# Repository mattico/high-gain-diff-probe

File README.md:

# High Gain Differential Probe

This was my attempt at a high gain (2000X) low-noise differential probe, for use in electronics testing.

Be warned that I haven't gotten this working. IIRC the issue was that it would oscillate or saturate. I didn't look into it too thoroughly, it's possible that there is an easy fix.

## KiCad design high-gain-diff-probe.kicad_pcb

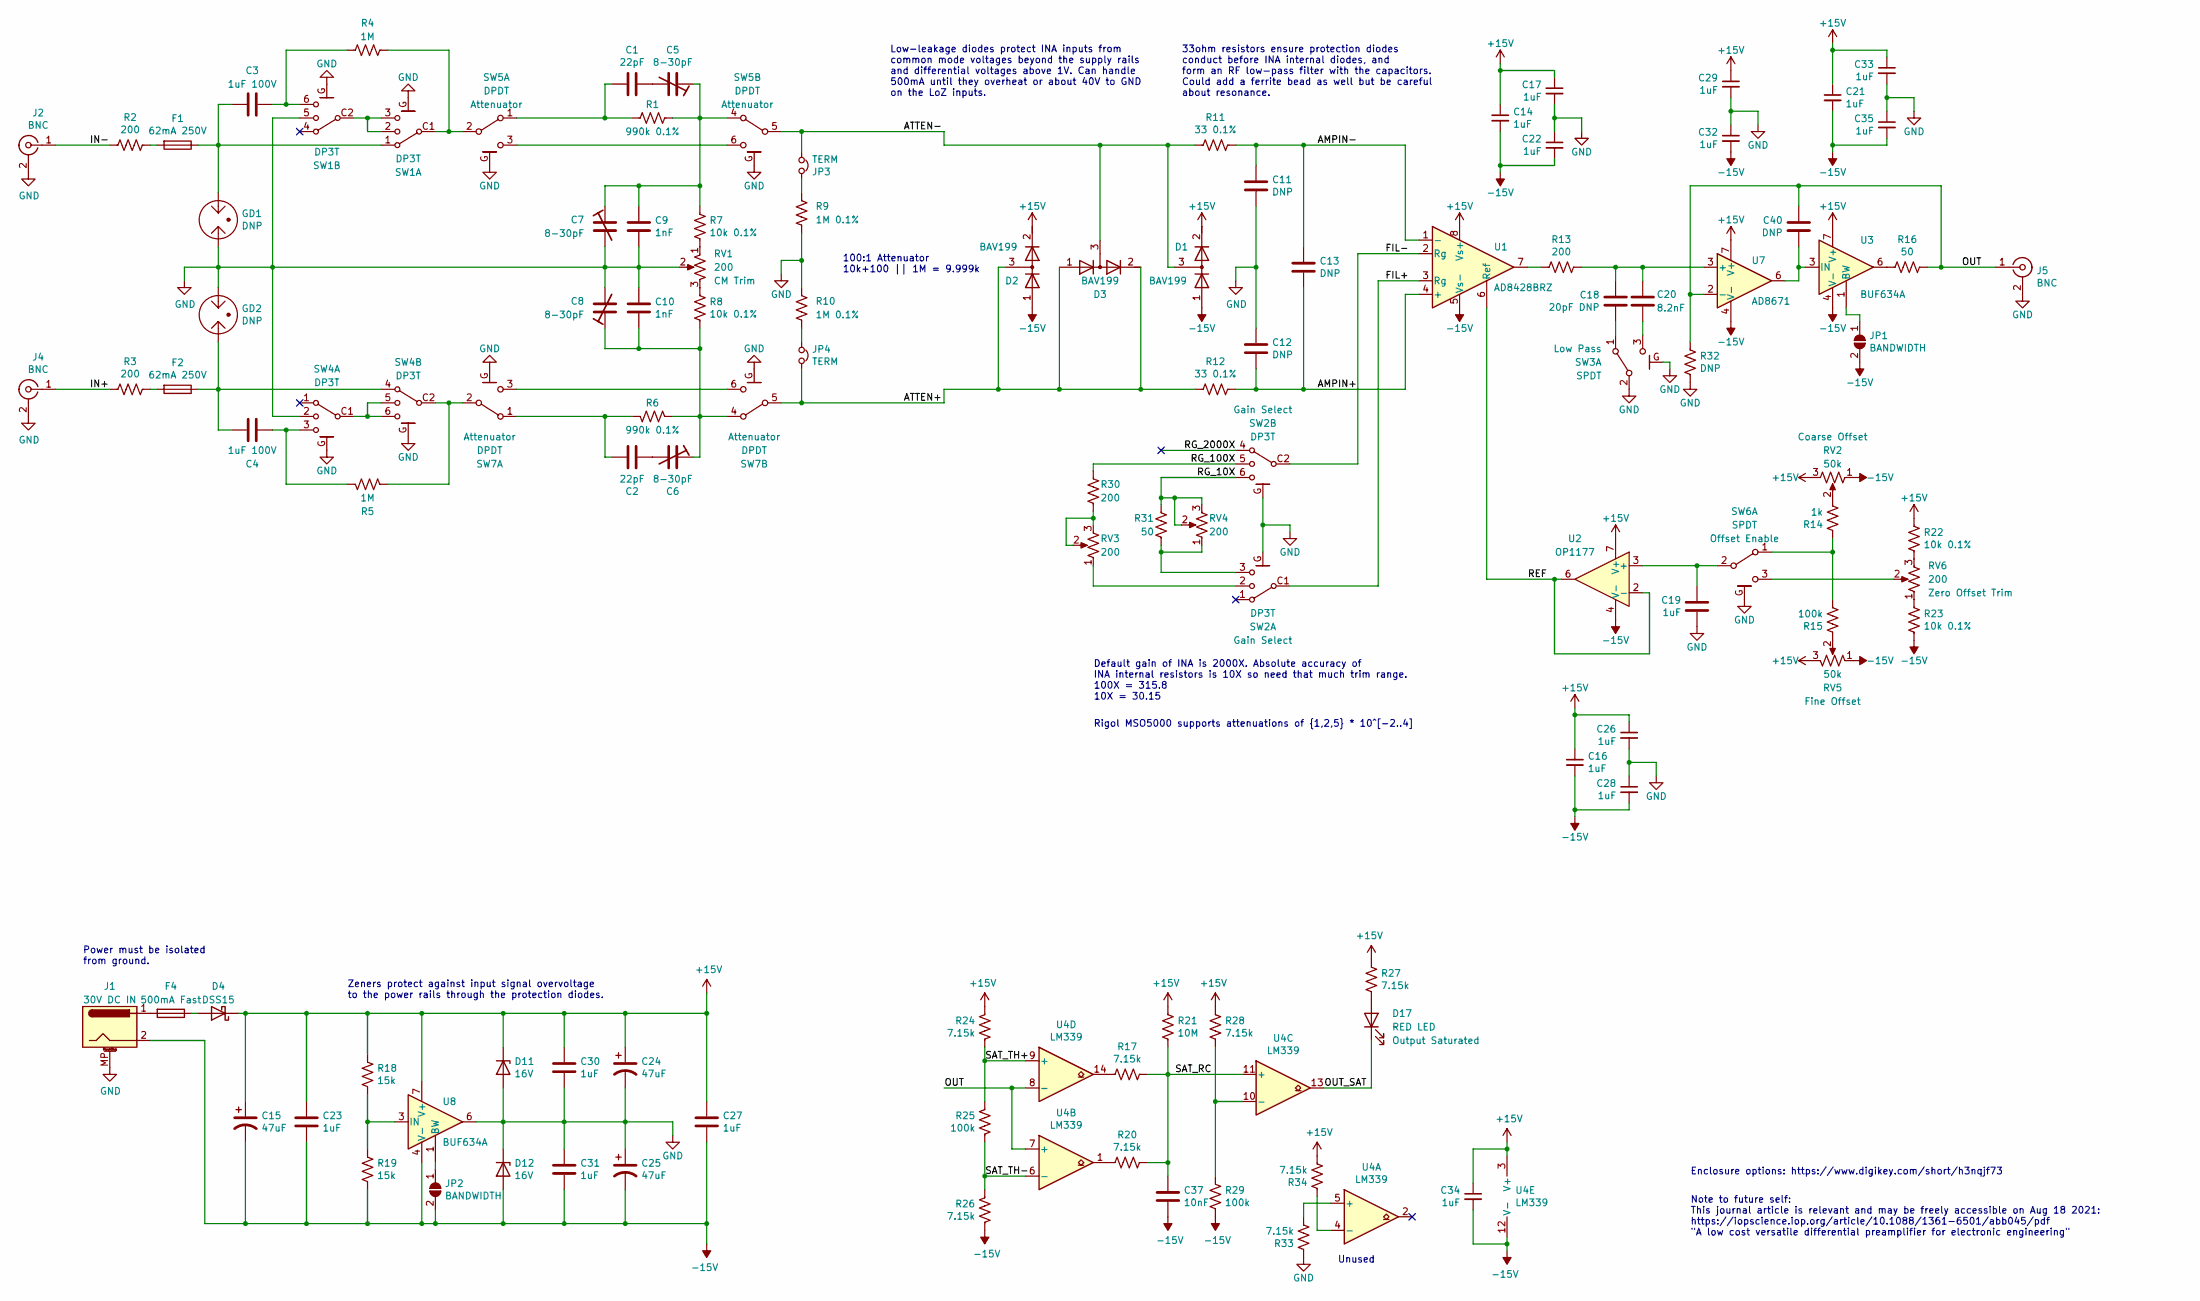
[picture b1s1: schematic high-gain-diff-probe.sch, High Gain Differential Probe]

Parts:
C1, C2: 22pF; C_0805_2012Metric_Pad1.15x1.40mm_HandSolder; MPN C0805C220J1GACTU
C3, C4: 1uF 100V; C_Rect_L7.2mm_W7.2mm_P5.00mm_FKS2_FKP2_MKS2_MKP2; MPN R82EC4100SH70J
C5, C6, C7, C8: 8-30pF; C_Trimmer_Voltronics_JZ; MPN SGC3S300
C9, C10: 1nF; C_0603_1608Metric_Pad1.05x0.95mm_HandSolder; MPN 0603N102F500CT
C11, C12, C13, C40: DNP; C_0603_1608Metric_Pad1.05x0.95mm_HandSolder
C14, C16, C17, C19, C21, C22, C23, C26, C27, C28, C29, C30, C31, C32, C33, C34, C35: 1uF; C_0603_1608Metric_Pad1.05x0.95mm_HandSolder; MPN CL10A105KL8NNNC
C15, C24, C25: 47uF; CP_Elec_6.3x7.7; MPN A768EB476M1VLAE042
C18: 20pF DNP; C_0603_1608Metric_Pad1.05x0.95mm_HandSolder
C20: 8.2nF; C_0603_1608Metric_Pad1.05x0.95mm_HandSolder; MPN GRM1885C1H822JA01D
C37: 10nF; C_0603_1608Metric_Pad1.05x0.95mm_HandSolder; MPN GRM188R72A103KA01J
D1, D2, D3: BAV199; SOT-23; MPN BAV199,215
D4: DSS15; D_SOD-123; MPN DSS15UTR
D11, D12: 16V; D_SMF; MPN BZD27C16
D17: RED LED; LED_D5.0mm; MPN 151051RS11000
F1, F2: 62mA 250V; Fuseholder_Cylinder-5x20mm_Schurter_FAB_0031-355x_Horizonta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; MPN 0031.3577
F4: 500mA Fast; Fuse_0805_2012Metric_Pad1.15x1.40mm_HandSolder; MPN F0805B0R50FWTR
GD1, GD2: DNP; GDT_Bourns_2031; MPN 2031-15T
J1: 30V DC IN; BarrelJack_CUI_PJ-063AH_Horizontal; MPN PJ-063AH
J2, J4, J5: BNC; BNC_Amphenol_B6252HB-NPP3G-50_Horizontal; MPN 0731385033
JP1, JP2: BANDWIDTH; SolderJumper-2_P1.3mm_Open_TrianglePad1.0x1.5mm
JP3, JP4: TERM; PinHeader_1x03_P2.54mm_Vertical; MPN PR20203VBNN
R1, R6: 990k 0.1%; R_1206_3216Metric_Pad1.30x1.75mm_HandSolder; MPN PTN1206E9903BST1
R2, R3: 200; R_MiniMELF_MMA-0204; MPN SMA-A0204BTNX180R
R4, R5: 1M; R_0603_1608Metric_Pad0.98x0.95mm_HandSolder; MPN RT0603BRD071ML
R7, R8, R22, R23: 10k 0.1%; R_0603_1608Metric_Pad0.98x0.95mm_HandSolder; MPN RT0603BRD1010KL
R9, R10: 1M 0.1%; R_0603_1608Metric_Pad0.98x0.95mm_HandSolder; MPN RT0603BRD071ML
R11, R12: 33 0.1%; R_0603_1608Metric_Pad0.98x0.95mm_HandSolder; MPN RT0603BRD0733RL
R13, R30: 200; R_0603_1608Metric_Pad0.98x0.95mm_HandSolder; MPN RMCF0603FT200R
R14: 1k; R_0603_1608Metric_Pad0.98x0.95mm_HandSolder; MPN CR0603-FX-1001ELF
R15, R25, R29: 100k; R_0603_1608Metric_Pad0.98x0.95mm_HandSolder; MPN RT0603FRE07100KL
R16: 50; R_1210_3225Metric_Pad1.30x2.65mm_HandSolder; MPN RMCF1210FT49R9
R17, R20, R24, R26, R27, R28, R33, R34: 7.15k; R_0603_1608Metric_Pad0.98x0.95mm_HandSolder; MPN RMCF0603FT7K15
R18, R19: 15k; R_0603_1608Metric_Pad0.98x0.95mm_HandSolder; MPN WR06X1502FTL
R21: 10M; R_0603_1608Metric_Pad0.98x0.95mm_HandSolder; MPN RMCF0603JT10M0
R31: 50; R_0603_1608Metric_Pad0.98x0.95mm_HandSolder; MPN RMCF0603FT49R9
R32: DNP; R_0603_1608Metric_Pad0.98x0.95mm_HandSolder
RV1, RV3, RV4, RV6: 200; Potentiometer_Bourns_3296Y_Vertical; MPN 67YR200LF
RV2, RV5: 50k; Potentiometer_Bourns_PTV09A-1_Single_Vertical; MPN PTV09A-4025F-B503
SW1, SW2, SW4: DP3T; SW_NKK_MRB24B; MPN MRB24B
SW3, SW6: SPDT; SW_TE_1825263-2_DPDT; MPN 1825263-2
SW5, SW7: DPDT; SW_TE_1825263-2_DPDT; MPN 1825263-2
U1: AD8428BRZ; SOIC-8_3.9x4.9mm_P1.27mm; MPN AD8428BRZ
U2: OP1177; SOIC-8_3.9x4.9mm_P1.27mm; MPN OP1177ARZ-REEL7
U3, U8: BUF634A; SOIC-8-1EP_3.9x4.9mm_P1.27mm_EP2.41x3.81mm_LargeThermalVias; MPN BUF634AIDDAR
U4: LM339; SOIC-14_3.9x8.7mm_P1.27mm; MPN NJM339CG-TE2
U7: AD8671; SOIC-8_3.9x4.9mm_P1.27mm; MPN AD8671ARZ-REEL7

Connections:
+15V: C14.1, C15.1, C16.1, C17.1, C21.1, C23.1, C24.1, C26.1, C27.1, C29.1, C30.1, C33.1, C34.1, D1.2 (K), D2.2 (K), D4.1 (K), D11.1 (K), R18.1, R21.2, R22.1, R24.2, R27.2, R28.2, R34.1, RV2.3, RV5.3, U1.8 (Vs+), U2.7 (V+), U3.7 (V+), U4.3 (V+), U7.7 (V+), U8.7 (V+)
-15V: C14.2, C15.2, C16.2, C21.2, C22.2, C23.2, C25.2, C27.2, C28.2, C31.2, C32.2, C34.2, C35.2, C37.1, D1.1 (A), D2.1 (A), D12.2 (A), J1.2, JP1.2 (B), JP2.2 (B), R19.2, R23.2, R26.1, R29.1, RV2.1, RV5.1, U1.5 (Vs-), U2.4 (V-), U3.4 (V-), U3.9 (PAD), U4.12 (V-), U7.4 (V-), U8.4 (V-), U8.9 (PAD)
/AMPIN+: C12.2, C13.2, R12.1, U1.4 (+)
/AMPIN-: C11.1, C13.1, R11.1, U1.1 (-)
/ATTEN+: D2.3 (common), D3.1 (A), D3.2 (K), JP4.2, R12.2, SW7.5 (B)
/ATTEN-: D1.3 (common), D3.3 (common), JP3.2, R11.2, SW5.5 (B)
/FIL+: SW2.C1 (C2), U1.3 (Rg)
/FIL-: SW2.C2, U1.2 (Rg)
/IN+: J4.1 (In), R3.2
/IN-: J2.1 (In), R2.2
/OUT: C40.1, J5.1 (In), R16.1, R32.1, U4.7 (+), U4.8 (-), U7.2 (-)
/OUT_SAT: D17.1 (K), U4.13
/REF: U1.6 (Ref), U2.2 (-), U2.6
/RG_10X: R31.2, RV4.2, RV4.3, SW2.6
/RG_100X: R30.1, SW2.5
/SAT_RC: C37.2, R17.1, R20.1, R21.1, U4.11 (+)
/SAT_TH+: R24.1, R25.2, U4.9 (+)
/SAT_TH-: R25.1, R26.2, U4.6 (-)
GND: C7.2, C8.2, C9.2, C10.1, C11.2, C12.1, C17.2, C19.1, C22.1, C24.2, C25.1, C26.2, C28.1, C29.2, C30.2, C31.1, C32.1, C33.2, C35.1, D11.2 (A), D12.1 (K), GD1.1, GD2.3, J1.MP (MountPin), J2.2 (Ext), J4.2 (Ext), J5.2 (Ext), R9.2, R10.1, R32.2, R33.2, RV1.2, SW1.5, SW1.G, SW2.G, SW3.2 (B), SW3.G, SW4.2 (5), SW4.G, SW5.G, SW6.G, SW7.G, U8.6
unnamed: C1.1, C5.2
unnamed: C1.2, R1.2, SW5.1 (A)
unnamed: C2.1, C6.2
unnamed: C2.2, R6.2, SW7.1 (A)
unnamed: C3.1, R4.1, SW1.6
unnamed: C3.2, F1.1, GD1.3, SW1.1 (4)
unnamed: C4.1, R5.1, SW4.3 (6)
unnamed: C4.2, F2.1, GD2.1, SW4.4
unnamed: C5.1, C7.1, C9.1, R1.1, R7.1, SW5.4 (A)
unnamed: C6.1, C8.1, C10.2, R6.1, R8.2, SW7.4 (A)
unnamed: C18.1, C20.1, R13.1, U7.3 (+)
unnamed: C18.2, SW3.1 (A)
unnamed: C19.2, SW6.2 (B), U2.3 (+)
unnamed: C20.2, SW3.3 (C)
unnamed: C40.2, U3.3 (IN), U7.6
unnamed: D4.2 (A), F4.1
unnamed: D17.2 (A), R27.1
unnamed: F1.2, R2.1
unnamed: F2.2, R3.1
unnamed: F4.2, J1.1
unnamed: JP1.1 (A), U3.1 (BW)
unnamed: JP2.1 (A), U8.1 (BW)
unnamed: JP3.1, R9.1
unnamed: JP4.1, R10.2
unnamed: R4.2, SW1.C1 (C2), SW5.2 (B)
unnamed: R5.2, SW4.C2, SW7.2 (B)
unnamed: R7.2, RV1.1
unnamed: R8.1, RV1.3
unnamed: R13.2, U1.7
unnamed: R14.1, R15.2, SW6.1 (A)
unnamed: R14.2, RV2.2
unnamed: R15.1, RV5.2
unnamed: R16.2, U3.6
unnamed: R17.2, U4.14
unnamed: R18.2, R19.1, U8.3 (IN)
unnamed: R20.2, U4.1
unnamed: R22.2, RV6.3
unnamed: R23.1, RV6.1
unnamed: R28.1, R29.2, U4.10 (-)
unnamed: R30.2, RV3.2, RV3.3
unnamed: R31.1, RV4.1, SW2.3 (6)
unnamed: R33.1, U4.5 (+)
unnamed: R34.2, U4.4 (-)
unnamed: RV3.1, SW2.2 (5)
unnamed: RV6.2, SW6.3 (C)
unnamed: SW1.2 (5), SW1.3 (6), SW1.C2
unnamed: SW4.5, SW4.6, SW4.C1 (C2)
unnamed: SW5.3 (C), SW5.6 (C)
unnamed: SW7.3 (C), SW7.6 (C)

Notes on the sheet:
Low-leakage diodes protect INA inputs from common mode voltages beyond the supply rails and differential voltages above 1V. Can handle 500mA until they overheat or about 40V to GND on the LoZ inputs.
33ohm resistors ensure protection diodes conduct before INA internal diodes, and form an RF low-pass filter with the capacitors. Could add a ferrite bead as well but be careful about resonance.
Default gain of INA is 2000X. Absolute accuracy of INA internal resistors is 10X so need that much trim range. 100X = 315.8 10X = 30.15
Rigol MSO5000 supports attenuations of {1,2,5} * 10^[-2..4]
100:1 Attenuator 10k+100 || 1M = 9.999k
Note to future self: This journal article is relevant and may be freely accessible on Aug 18 2021: https://iopscience.iop.org/article/10.1088/1361-6501/abb045/pdf "A low cost versatile differential preamplifier for electronic engineering"
Enclosure options: https://www.digikey.com/short/h3nqjf73
Power must be isolated from ground.
Zeners protect against input signal overvoltage to the power rails through the protection diodes.
Unused

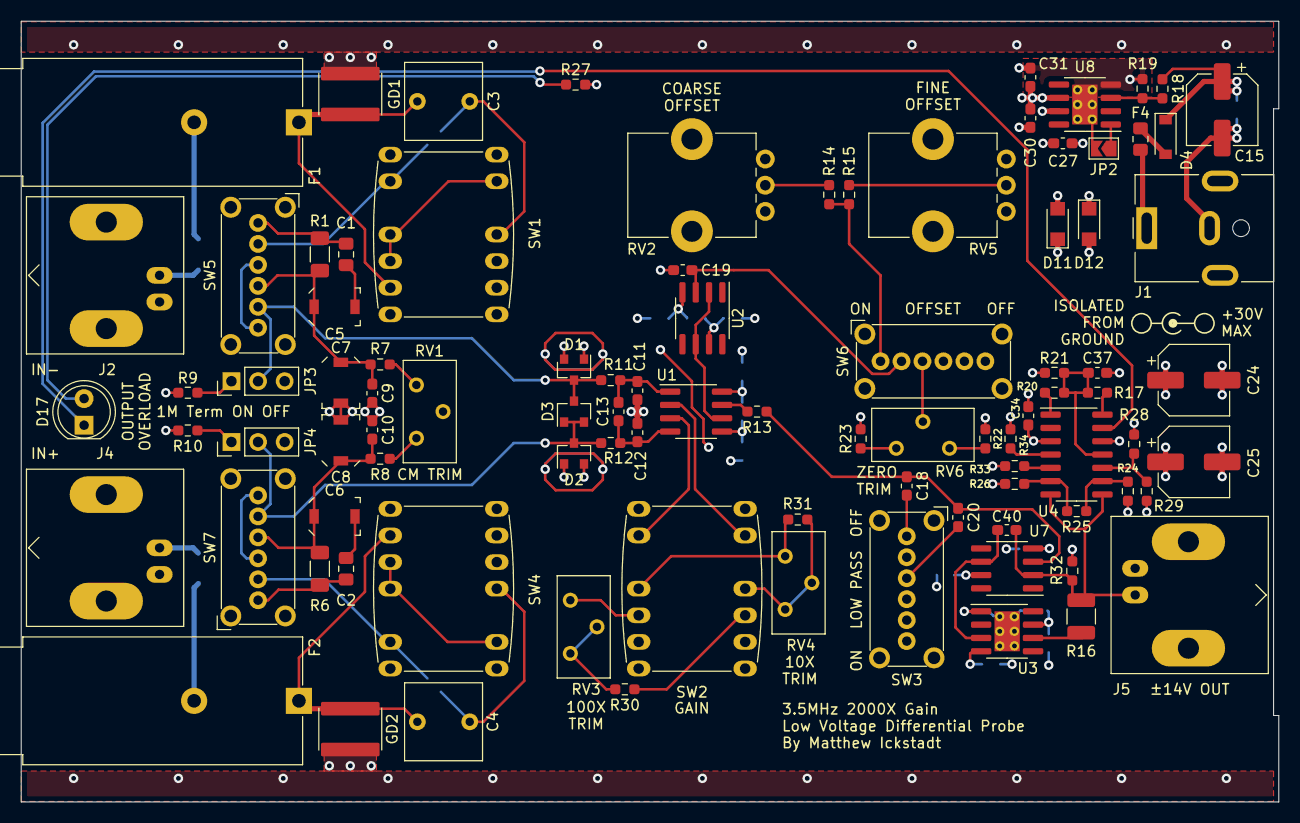
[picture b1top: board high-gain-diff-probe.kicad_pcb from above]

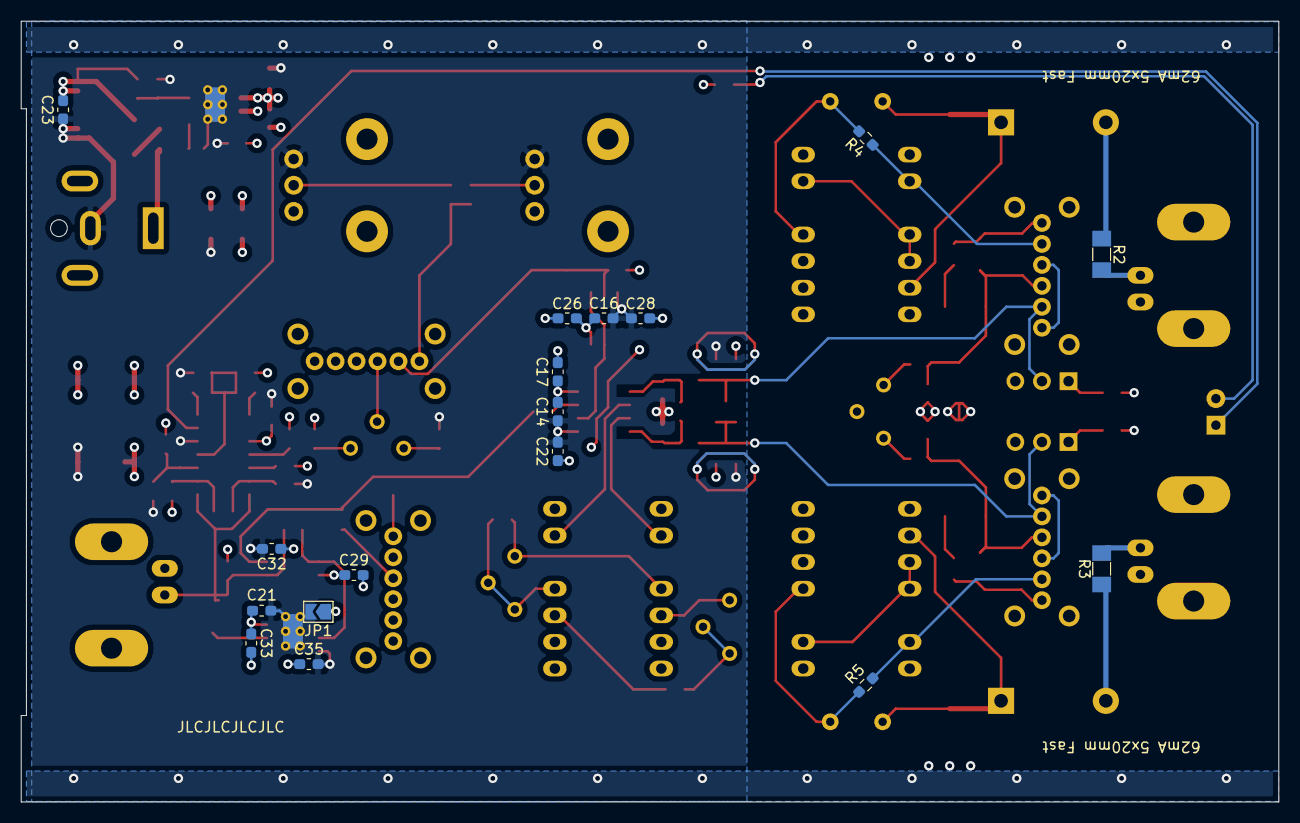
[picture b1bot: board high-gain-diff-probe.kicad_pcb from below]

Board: 4 copper layers, 120.0 x 74.5 mm, 110 parts (17 on the bottom side), 68 nets.

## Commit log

2021-04-16 Add LTSpice simulation
2021-04-16 Schematic 1st pass
2021-04-16 Transformer driver?
2021-04-16 Developing
2021-04-17 Improve input divider ratio
2021-04-17 Improve simulations
2021-04-17 Implement capacitance multiplier, power overvoltage protection, and signal out of range comparators
2021-04-17 Add notes to schematic
2021-04-17 Add footprints to most parts
2021-04-17 Add footprints for everything
2021-04-17 Begin layout
2021-04-18 Continue layout
2021-04-20 Reworking
2021-04-20 Use different knobs for attenutator and gain
2021-04-20 'finish' analog section
2021-04-21 Implement boost power
2021-04-21 Try out other power supplies
2021-04-22 Simplify power
2021-04-22 Layout
2021-04-23 More layout
2021-04-23 Tweaks
2021-04-24 Add 3D Models
2021-04-24 Finish Layout
2021-04-24 Add images, layout tweaks.
2021-04-24 Add info to silkscreen
2021-04-24 Add Gerbers
2021-04-24 Use larger thermal vias for cheaper PCBs
2021-04-24 Connect thermal vias to plane solidly
2021-04-24 Add MPNs for everything else
2021-04-25 Add mechanical models. Tweak LED Position.
2021-04-25 Tweak layout
2021-04-25 Fix 10K MPN
2021-04-25 Update images, gerbers
2021-04-26 Begin work on new version with no relays and manual attenuator switching
2021-04-27 Complete major layout of no-relay design
2021-04-27 Layout Tweaks
2021-04-27 Update gerbers and 3d models
2021-04-27 Overengineer Comparator
2021-04-28 Fix AC coupling resistor
2021-05-01 Update gerbers
2021-05-12 Fix termination
